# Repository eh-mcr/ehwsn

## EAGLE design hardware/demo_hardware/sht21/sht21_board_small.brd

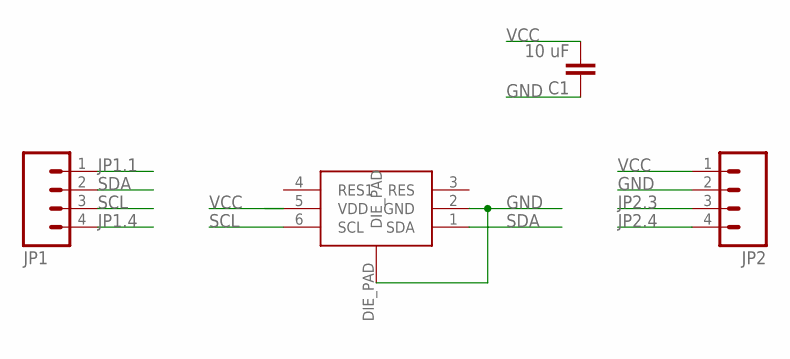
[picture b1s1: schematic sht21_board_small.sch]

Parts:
C1: 10 uF; 0805
JP1, JP2: M04PTH; 1X04
U$1: SHT21; SHT21_PADS

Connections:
GND: C1.1, JP2.2, U$1.2 (GND), U$1.DIE_PAD
JP1.1: JP1.1
JP1.4: JP1.4
JP2.3: JP2.3
JP2.4: JP2.4
SCL: JP1.3, U$1.6 (SCL)
SDA: JP1.2, U$1.1 (SDA)
VCC: C1.2, JP2.1, U$1.5 (VDD)

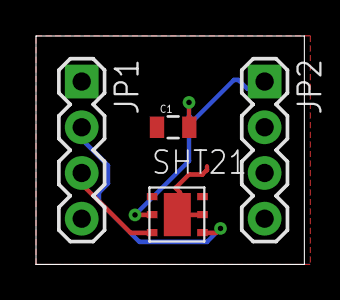
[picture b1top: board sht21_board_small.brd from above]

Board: 2 copper layers, 14.9 x 12.7 mm, 4 parts (0 on the bottom side), 4 nets.

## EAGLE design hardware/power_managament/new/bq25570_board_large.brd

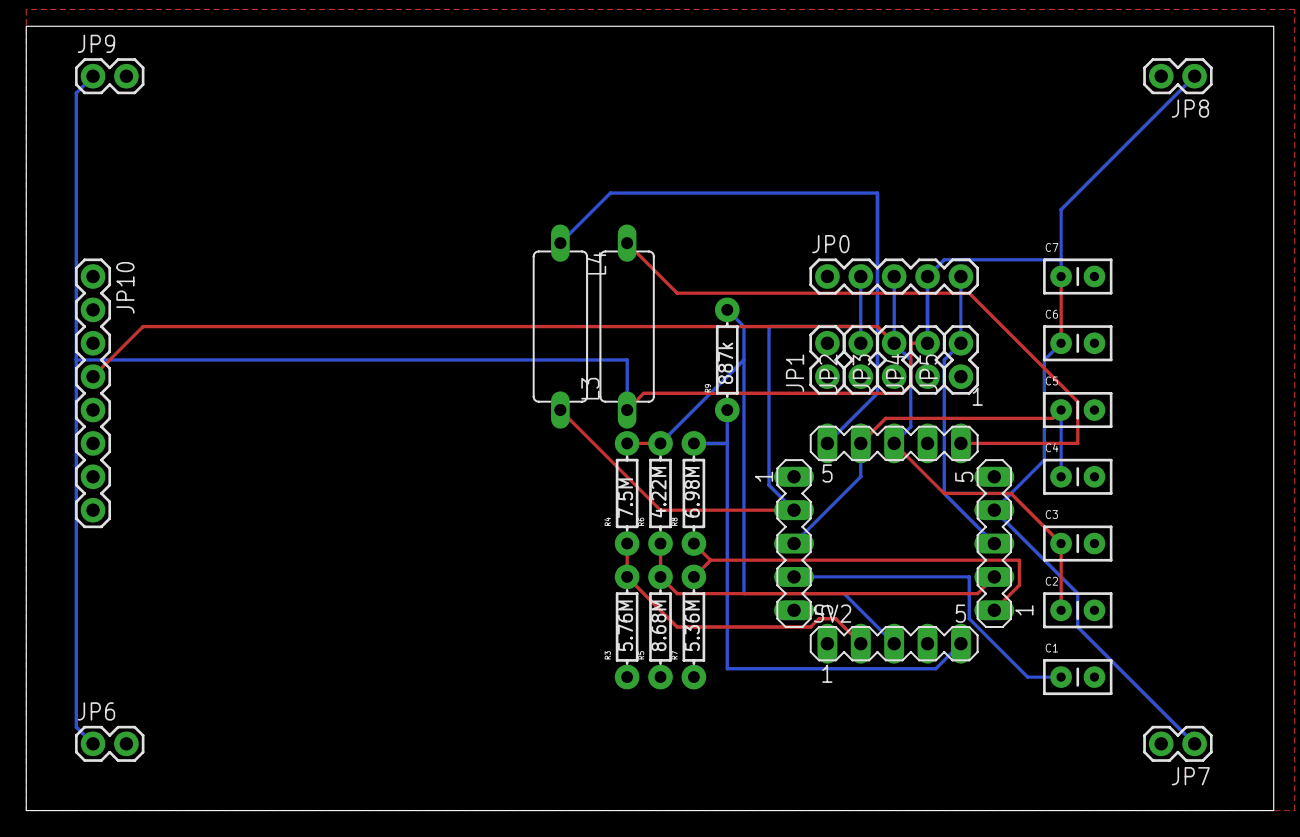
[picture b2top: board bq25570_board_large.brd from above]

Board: 2 copper layers, 94.9 x 59.7 mm, 28 parts (0 on the bottom side), 14 nets.

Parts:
C1: 0.01uF; CAP-PTH-SMALLEZ
C2, C3: 100uF; CAP-PTH-SMALLEZ
C4: 4.7uF; CAP-PTH-SMALLEZ
C5: 0.1uF; CAP-PTH-SMALLEZ
C6: 22uF; CAP-PTH-SMALLEZ
C7: 1000uF; CAP-PTH-SMALLEZ
JP0: 1X05
JP1, JP2, JP3, JP4, JP5, JP6, JP7, JP8, JP9: 1X02
JP10: 1X08_ROUND
L3: 10uH; BC12
L4: 22uH; BC12
R3: 5.76M; AXIAL-0.3
R4: 7.5M; AXIAL-0.3
R5: 8.68M; AXIAL-0.3
R6: 4.22M; AXIAL-0.3
R7: 5.36M; AXIAL-0.3
R8: 6.98M; AXIAL-0.3
R9: 887k; AXIAL-0.3
SV2: MA05-1

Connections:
LBOOST: L4.1, SV2.20
LBUCK: L3.2, SV2.16
OK_HYST: R8.P$2, R9.P$1, SV2.10
OK_PROG: R7.P$2, R8.P$1, SV2.11
VBAT: C2.1, C3.1, JP0.3, JP3.2, JP10.4, SV2.18
VBAT_OK: JP0.5, JP5.2, SV2.13
VBAT_OV: R3.P$2, R4.P$1, SV2.7
VIN: JP0.2, JP2.2, L4.2, SV2.2
VOUT: C6.1, C7.1, JP0.4, JP4.2, JP6.1, JP7.1, JP8.1, JP9.1, L3.1, SV2.14
VOUT_SET: R5.P$2, R6.P$1, SV2.12
VRDIV: R4.P$2, R6.P$2, R9.P$2, SV2.8
VREF_SAMP: C1.1, SV2.4
VSS: C1.2, C2.2, C3.2, C4.2, C5.2, C6.2, C7.2, JP0.1, JP1.1, JP1.2, JP2.1, JP3.1, JP4.1, JP5.1, JP6.2, JP7.2, JP8.2, JP9.2, JP10.8, R3.P$1, R5.P$1, R7.P$1, SV2.1, SV2.5, SV2.6, SV2.9, SV2.15, SV2.17
VSTOR: C4.1, C5.1, SV2.3, SV2.19

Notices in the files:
parts and their libraries:
SparkFun-Passives: Licensing: Creative Commons ShareAlike 4.0 International - https://creativecommons.org/licenses/by-sa/4.0
